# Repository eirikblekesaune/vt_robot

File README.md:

vt_robot
========

All robot patches and code for Verdensteatret

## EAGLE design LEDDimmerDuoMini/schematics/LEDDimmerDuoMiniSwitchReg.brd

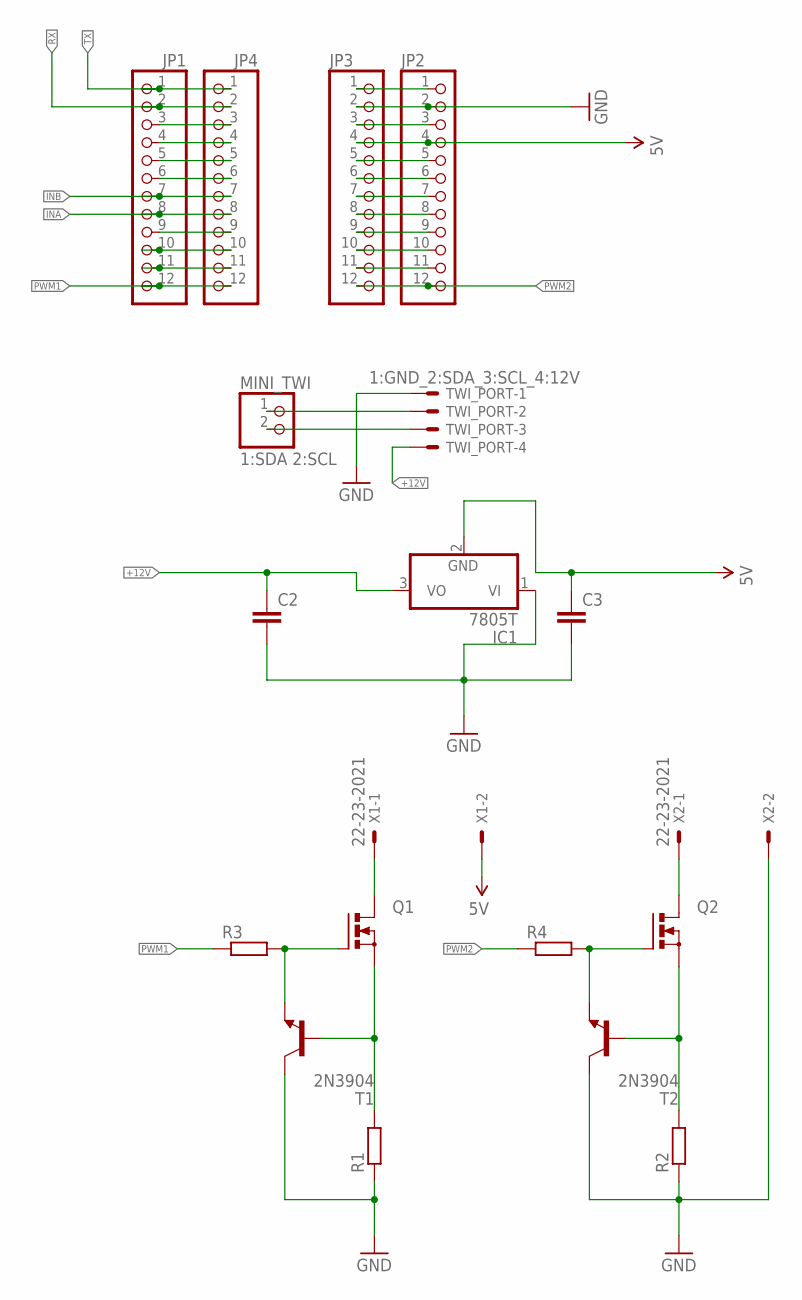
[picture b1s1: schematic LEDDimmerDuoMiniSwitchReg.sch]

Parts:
C2, C3: CAP0603-CAP; 0603-CAP
IC1: 7805T; TO220H
JP1, JP2, JP3, JP4: PINHD-1X12; 1X12
MINI_TWI: 1:SDA 2:SCL; 1X02
Q1, Q2: PMOSFET_NTO220BV; TO220BV
R1, R2: R-EU_VTA52; VTA52
R3, R4: R; R0805
T1, T2: 2N3904; TO92
TWI_PORT: 1:GND_2:SDA_3:SCL_4:12V; 22-23-2041
X1, X2: 22-23-2021

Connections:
5V: C3.1, IC1.2 (GND), JP2.4, JP3.4, X1.2
+12V: C2.1, IC1.3 (VO), TWI_PORT.4
GND: C2.2, C3.2, IC1.1 (VI), JP2.2, JP3.2, R1.1, R2.1, T1.1 (C), T2.1 (C), TWI_PORT.1, X2.2
INA: JP1.8, JP4.8
INB: JP1.7, JP4.7
unnamed: MINI_TWI.1, TWI_PORT.2
unnamed: MINI_TWI.2, TWI_PORT.3
unnamed: Q1.S, R1.2, T1.2 (B)
unnamed: Q2.S, R2.2, T2.2 (B)
unnamed: JP1.3, JP4.3
unnamed: Q2.G, R4.2, T2.3 (E)
unnamed: JP1.4, JP4.4
unnamed: JP1.5, JP4.5
unnamed: JP1.11, JP4.11
unnamed: JP1.10, JP4.10
unnamed: JP1.6, JP4.6
unnamed: JP1.9, JP4.9
unnamed: JP2.1, JP3.1
unnamed: JP2.3, JP3.3
unnamed: JP2.5, JP3.5
unnamed: JP2.6, JP3.6
unnamed: JP2.7, JP3.7
unnamed: JP2.8, JP3.8
unnamed: JP2.9, JP3.9
unnamed: JP2.10, JP3.10
unnamed: JP2.11, JP3.11
unnamed: Q1.D, X1.1
unnamed: Q2.D, X2.1
PWM1: JP1.12, JP4.12, Q1.G, R3.1, R3.2, T1.3 (E)
PWM2: JP2.12, JP3.12, R4.1
RX: JP1.2, JP4.2
TX: JP1.1, JP4.1

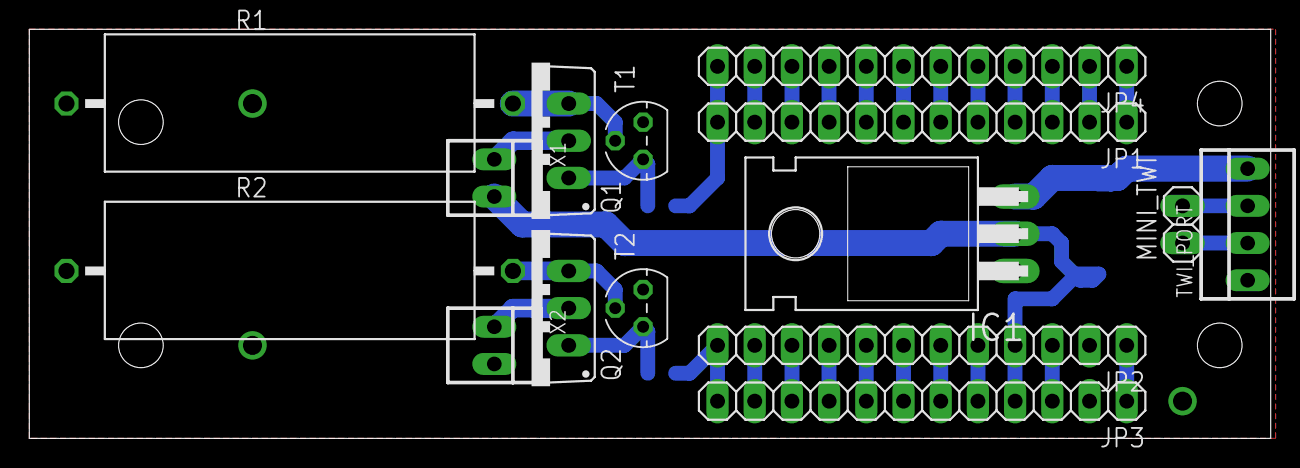
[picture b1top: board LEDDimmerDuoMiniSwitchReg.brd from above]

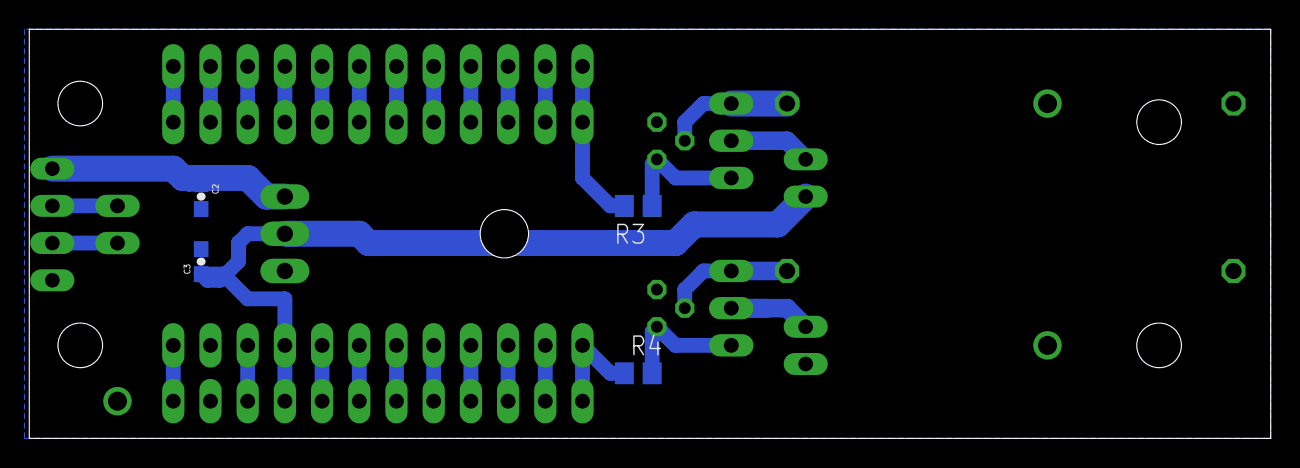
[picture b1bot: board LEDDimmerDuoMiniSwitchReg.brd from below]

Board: 2 copper layers, 84.8 x 27.9 mm, 19 parts (4 on the bottom side), 32 nets.

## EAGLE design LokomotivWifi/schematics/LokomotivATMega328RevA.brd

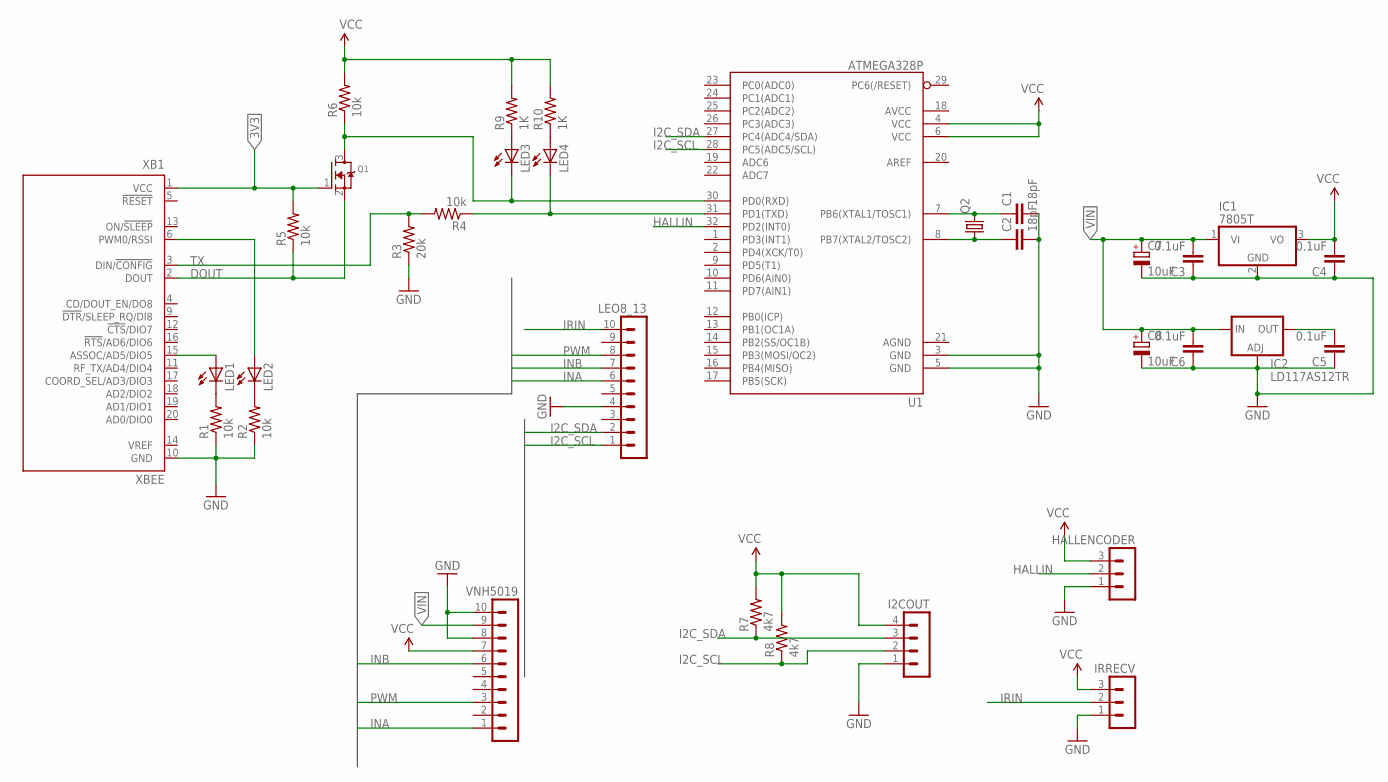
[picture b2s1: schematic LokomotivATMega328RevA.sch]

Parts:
C1, C2: 18pF; 0603-CAP
C3, C4, C5, C6: 0.1uF; 0603-CAP
C7, C8: 10uF; E3,5-10
HALLENCODER: MA03-1
I2COUT: MA04-1
IC1: 7805T; TO220H
IC2: LD117AS12TR; SOT223
IRRECV: MA03-1
LED1, LED2, LED3, LED4: LED-FKIT-1206; FKIT-LED-1206
LEO8_13: MA10-1
Q1: MOSFET-NREFLOW; SOT23
Q2: CRYSTALSM49; SM49
R1, R2, R4, R5, R6: 10k; R0805
R3: 20k; R0805
R7, R8: 4k7; R0805
R9, R10: 1K; R0805
U1: ATMEGA328P; TQFP32-08
VNH5019: MA10-1
XB1: XBEE

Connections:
3V3: Q1.1 (G), R5.2, XB1.1 (VCC)
DOUT: Q1.2 (S), R5.1, XB1.2 (DOUT)
GND: C1.2, C2.2, C3.1, C4.1, C5.1, C6.1, C7.-, C8.-, HALLENCODER.1, I2COUT.1, IC1.2 (GND), IC2.1 (ADJ), IRRECV.1, LEO8_13.4, R1.1, R2.1, R3.1, U1.3 (GND), U1.5 (GND), VNH5019.8, VNH5019.10, XB1.10 (GND)
HALLIN: HALLENCODER.2, U1.32 (PD2(INT0))
I2C_SCL: I2COUT.2, LEO8_13.1, R8.1, U1.28 (PC5(ADC5/SCL))
I2C_SDA: I2COUT.3, LEO8_13.2, R7.1, U1.27 (PC4(ADC4/SDA))
INA: LEO8_13.6, VNH5019.1
INB: LEO8_13.7, VNH5019.6
IRIN: IRRECV.2, LEO8_13.10
unnamed: LED1.C, R1.2
unnamed: LED2.C, R2.2
unnamed: LED1.A, XB1.15 (ASSOC/AD5/DIO5)
unnamed: LED2.A, XB1.6 (PWM0/RSSI)
unnamed: LED3.C, Q1.3 (D), R6.1, U1.30 (PD0(RXD))
unnamed: LED3.A, R9.1
unnamed: LED4.A, R10.1
unnamed: C1.1, Q2.2, U1.7 (PB6(XTAL1/TOSC1))
unnamed: LED4.C, R4.1, U1.31 (PD1(TXD))
unnamed: C2.1, Q2.1, U1.8 (PB7(XTAL2/TOSC2))
unnamed: C5.2, IC2.4 (OUT)
PWM: LEO8_13.8, VNH5019.3
TX: R3.2, R4.2, XB1.3 (DIN/!CONFIG)
VCC: C4.2, HALLENCODER.3, I2COUT.4, IC1.3 (VO), IRRECV.3, R6.2, R7.2, R8.2, R9.2, R10.2, U1.4 (VCC), U1.6 (VCC), VNH5019.7
VIN: C3.2, C6.2, C7.+, C8.+, IC1.1 (VI), IC2.3 (IN), VNH5019.9

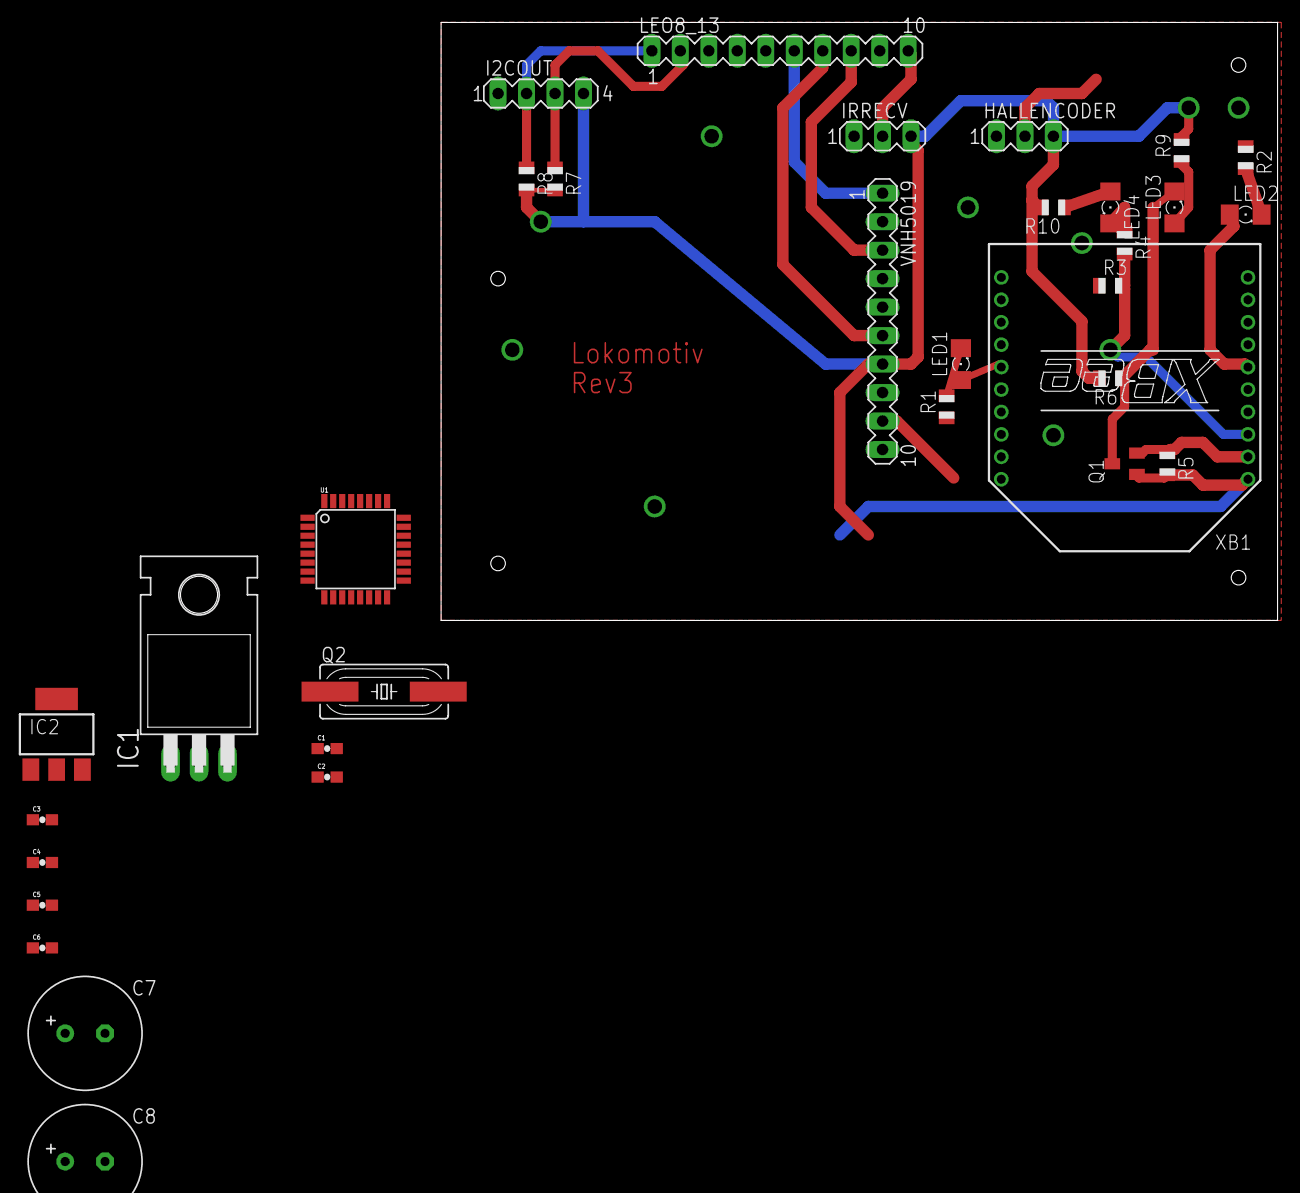
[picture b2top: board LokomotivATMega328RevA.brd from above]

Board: 2 copper layers, 74.6 x 53.3 mm, 33 parts (0 on the bottom side), 24 nets.

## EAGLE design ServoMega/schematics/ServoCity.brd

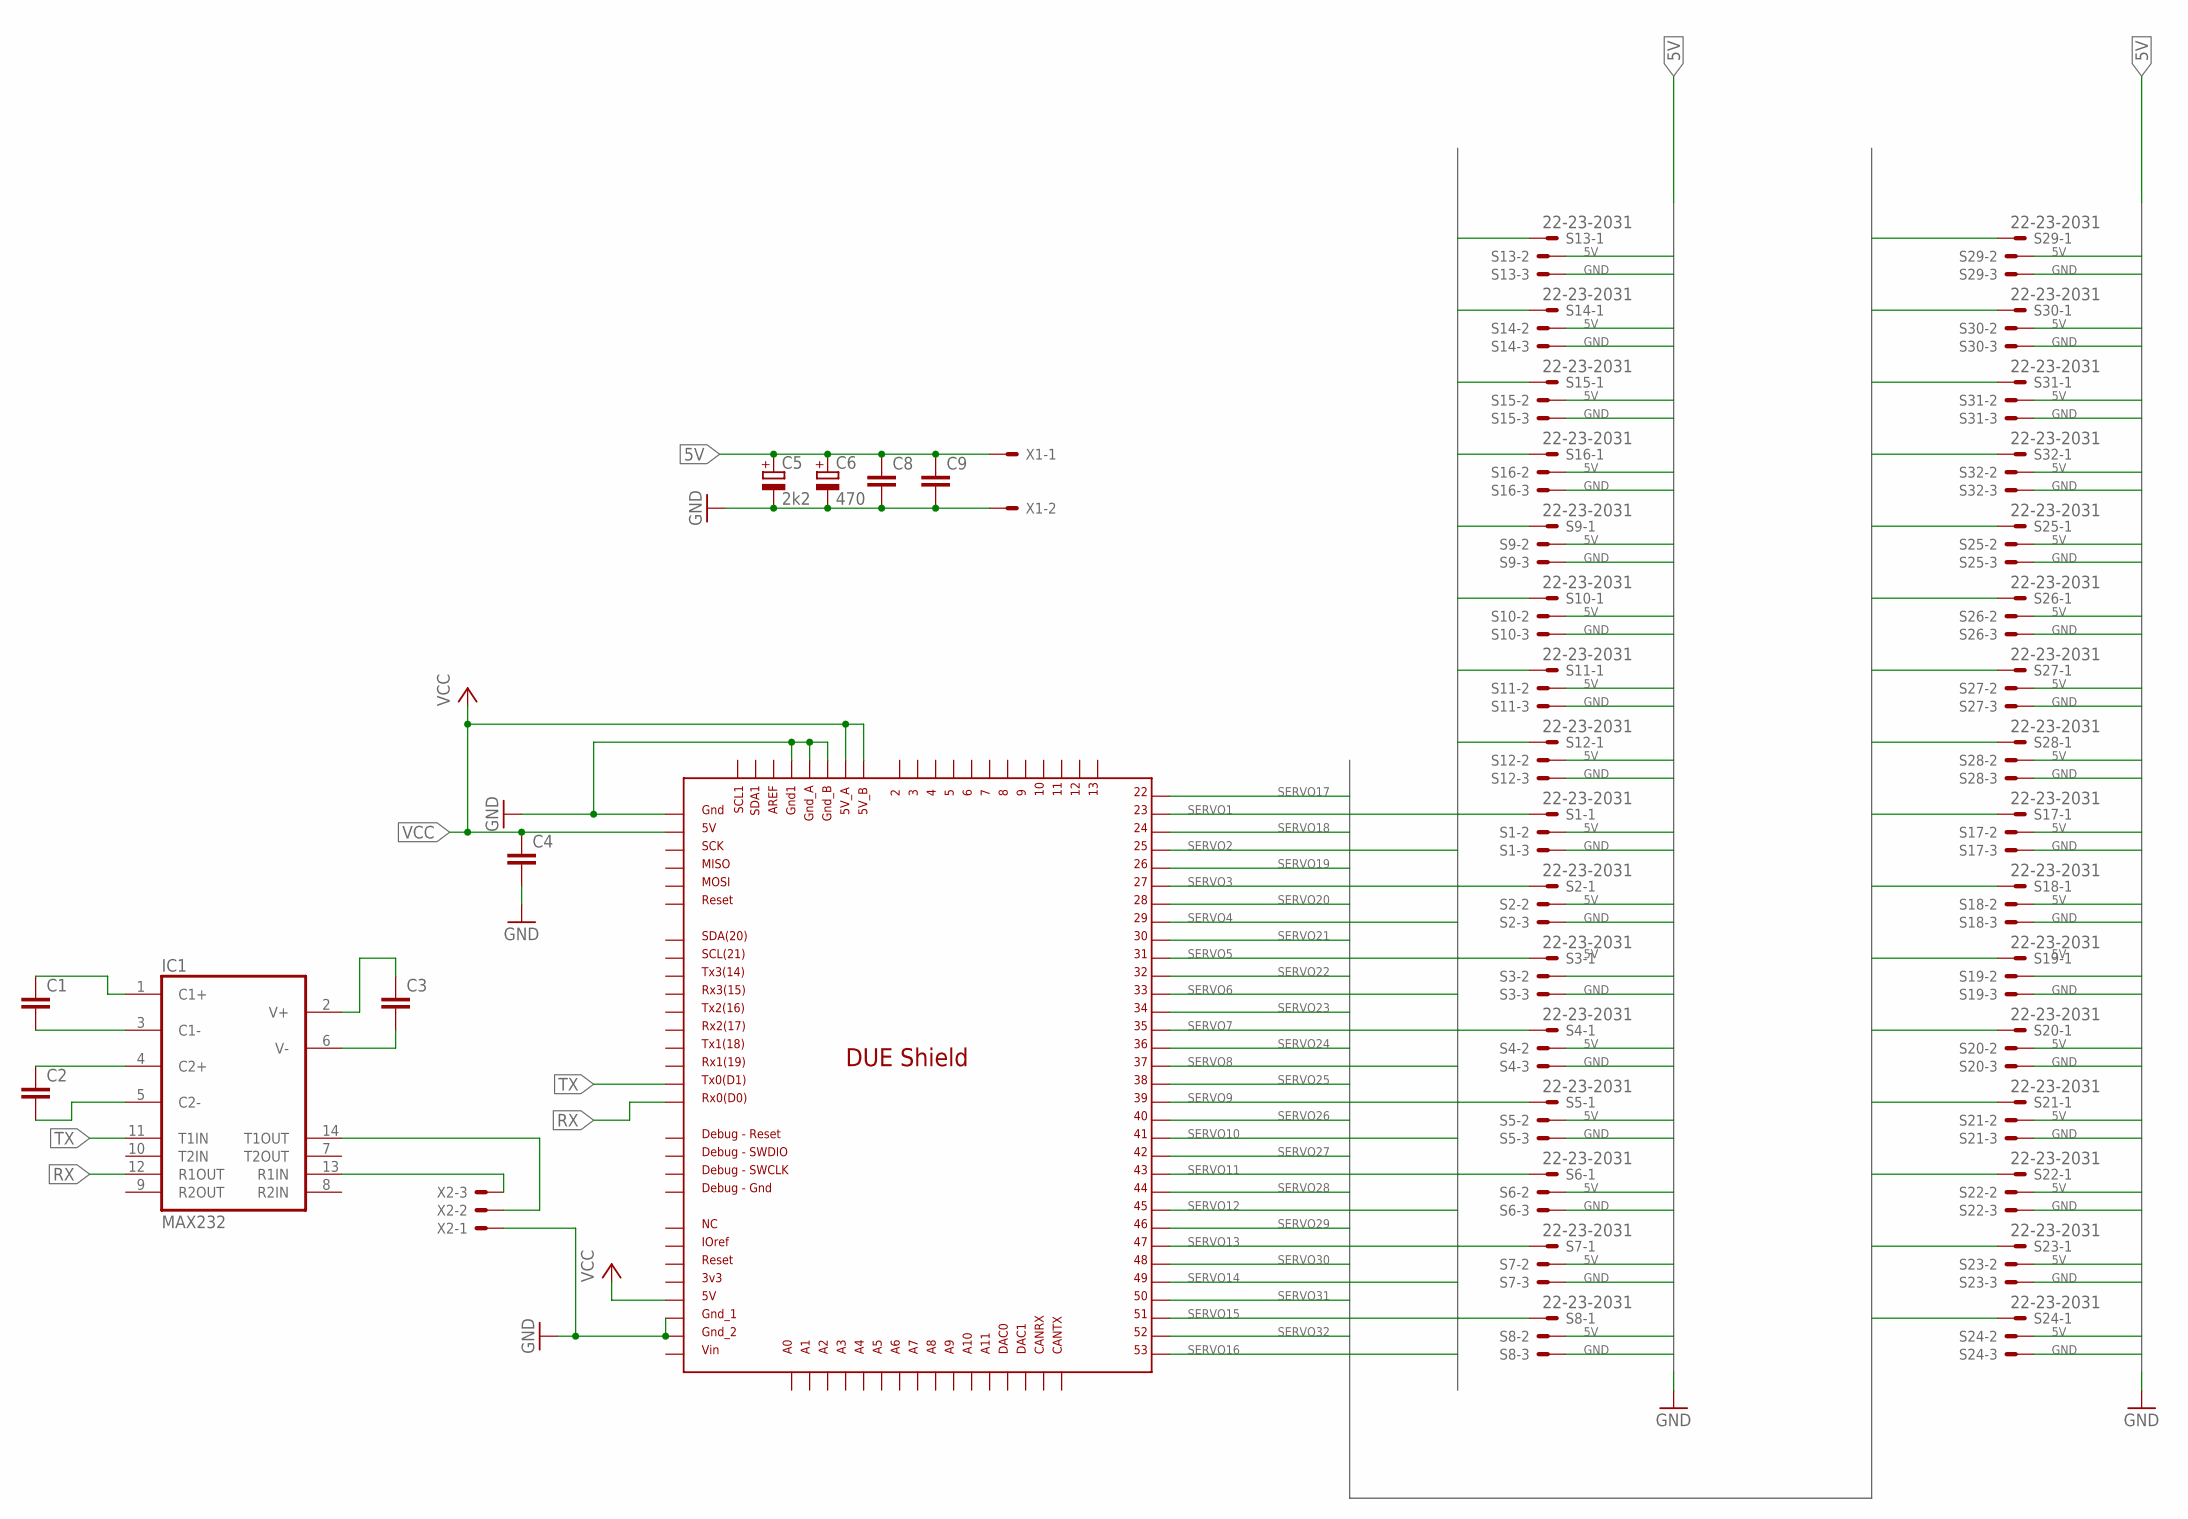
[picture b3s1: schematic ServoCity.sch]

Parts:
C1, C2, C3, C4: C-EUC0805; C0805
C5: 2k2; EB20D
C6: 470; E5-10,5
C8, C9: C; C0805
IC1: MAX232; DIL16
S1, S2, S3, S4, S5, S6, S7, S8, S9, S10, S11, S12, S13, S14, S15, S16, S17, S18, S19, S20, S21, S22, S23, S24, S25, S26, S27, S28, S29, S30, S31, S32: 22-23-2031
U$1: DUE(NORMAL)
X1: KK-156-2
X2: KK-156-3

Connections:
5V: C5.+, C6.+, C8.1, C9.1, S1.2, S2.2, S3.2, S4.2, S5.2, S6.2, S7.2, S8.2, S9.2, S10.2, S11.2, S12.2, S13.2, S14.2, S15.2, S16.2, S17.2, S18.2, S19.2, S20.2, S21.2, S22.2, S23.2, S24.2, S25.2, S26.2, S27.2, S28.2, S29.2, S30.2, S31.2, S32.2, X1.1
GND: C4.2, C5.-, C6.-, C8.2, C9.2, IC1.15 (GND), S1.3, S2.3, S3.3, S4.3, S5.3, S6.3, S7.3, S8.3, S9.3, S10.3, S11.3, S12.3, S13.3, S14.3, S15.3, S16.3, S17.3, S18.3, S19.3, S20.3, S21.3, S22.3, S23.3, S24.3, S25.3, S26.3, S27.3, S28.3, S29.3, S30.3, S31.3, S32.3, U$1.5V_ICSP, U$1.GND1, U$1.GND_1, U$1.GND_2, U$1.GND_A, U$1.GND_B, X1.2, X2.1
unnamed: IC1.14 (T1OUT), X2.2
unnamed: IC1.13 (R1IN), X2.3
unnamed: C1.1, IC1.1 (C1+)
unnamed: C1.2, IC1.3 (C1-)
unnamed: C2.1, IC1.4 (C2+)
unnamed: C2.2, IC1.5 (C2-)
unnamed: C3.1, IC1.2 (V+)
unnamed: C3.2, IC1.6 (V-)
RX: IC1.12 (R1OUT), U$1.RX0
SERVO1: S1.1, U$1.23
SERVO2: S2.1, U$1.25
SERVO3: S3.1, U$1.27
SERVO4: S4.1, U$1.29
SERVO5: S5.1, U$1.31
SERVO6: S6.1, U$1.33
SERVO7: S7.1, U$1.35
SERVO8: S8.1, U$1.37
SERVO9: S9.1, U$1.39
SERVO10: S10.1, U$1.41
SERVO11: S11.1, U$1.43
SERVO12: S12.1, U$1.45
SERVO13: S13.1, U$1.47
SERVO14: S14.1, U$1.49
SERVO15: S15.1, U$1.51
SERVO16: S16.1, U$1.53
SERVO17: S17.1, U$1.22
SERVO18: S18.1, U$1.24
SERVO19: S19.1, U$1.26
SERVO20: S20.1, U$1.28
SERVO21: S21.1, U$1.30
SERVO22: S22.1, U$1.32
SERVO23: S23.1, U$1.34
SERVO24: S24.1, U$1.36
SERVO25: S25.1, U$1.38
SERVO26: S26.1, U$1.40
SERVO27: S27.1, U$1.42
SERVO28: S28.1, U$1.44
SERVO29: S29.1, U$1.46
SERVO30: S30.1, U$1.48
SERVO31: S31.1, U$1.50
SERVO32: S32.1, U$1.52
TX: IC1.11 (T1IN), U$1.TX0
VCC: C4.1, IC1.16 (VCC), U$1.5V, U$1.5V_A, U$1.5V_B, U$1.GND_ICSP

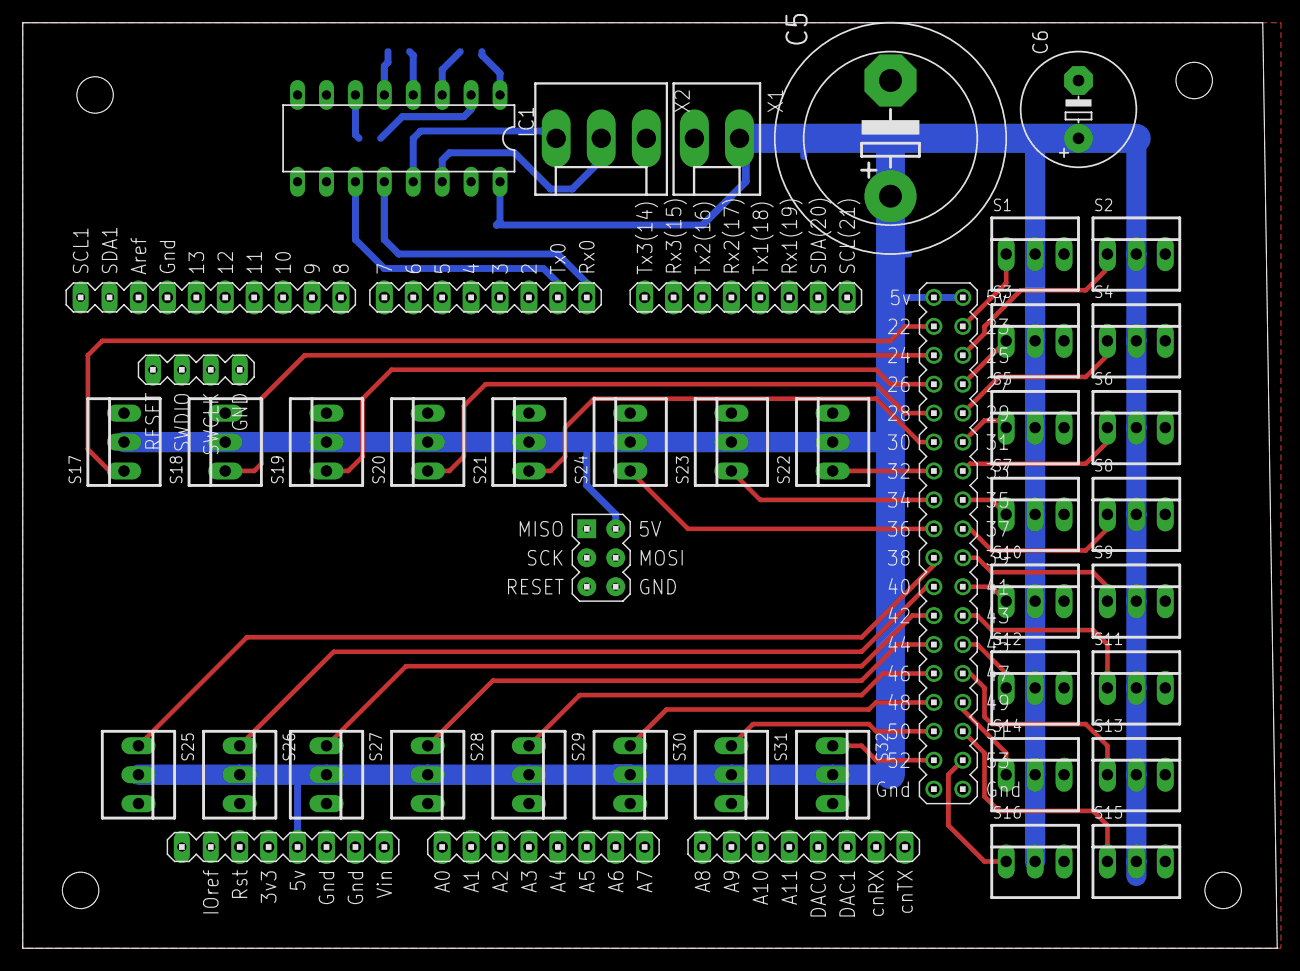
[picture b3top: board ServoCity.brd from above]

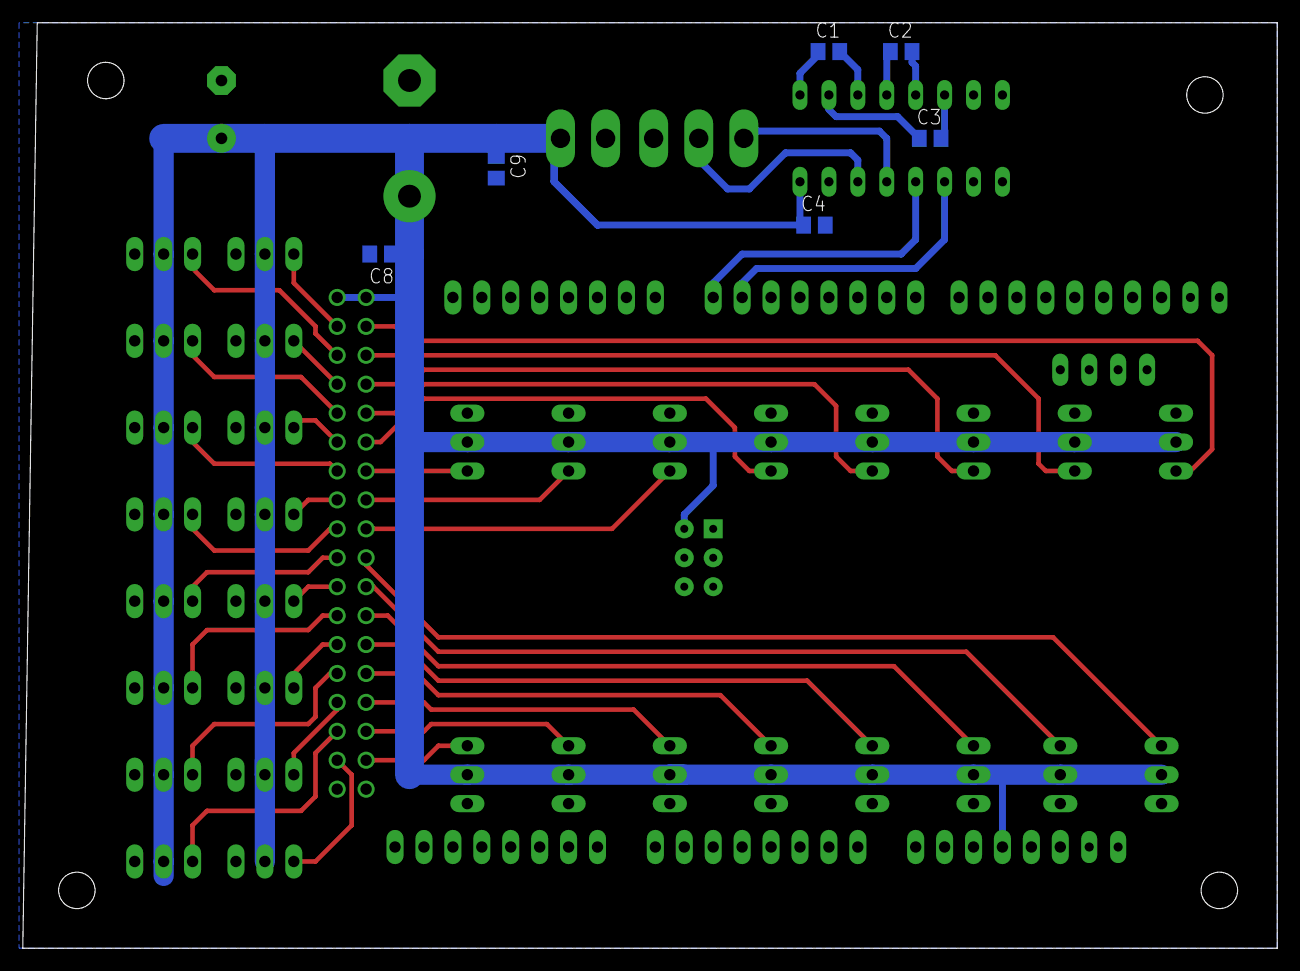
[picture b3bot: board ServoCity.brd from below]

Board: 2 copper layers, 110.2 x 81.3 mm, 44 parts (6 on the bottom side), 45 nets.

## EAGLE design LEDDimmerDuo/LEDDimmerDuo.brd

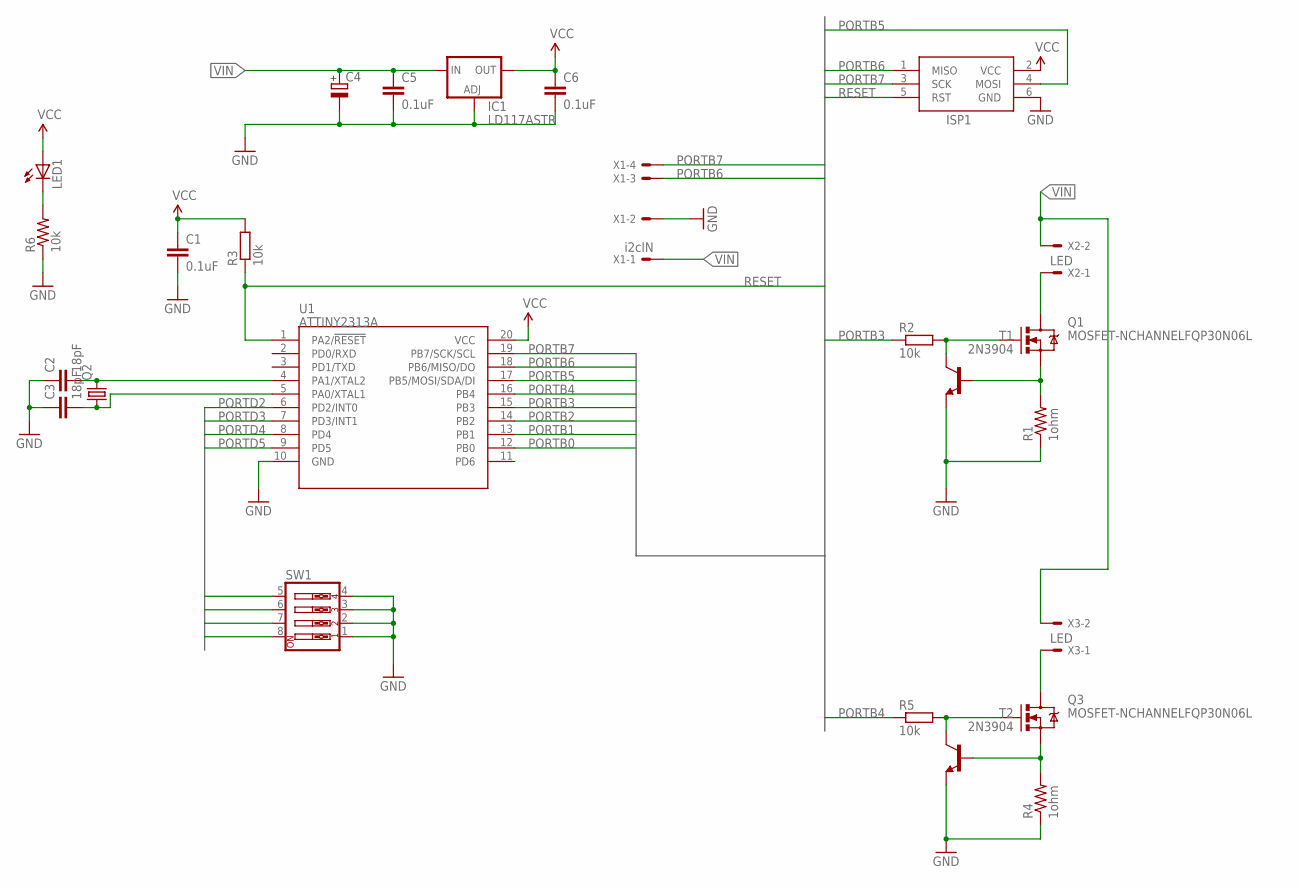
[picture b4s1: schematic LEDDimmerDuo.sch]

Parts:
C1, C5, C6: 0.1uF; 0805
C2, C3: 18pF; 0805
C4: CPOL-EUE3.5-10; E3,5-10
IC1: LD117ASTR; SOT223
ISP1: AVRISP-6; AVRISP
LED1: LED0603; LED-0603
Q1, Q3: MOSFET-NCHANNELFQP30N06L; TO220V
Q2: CRYSTALSM49; SM49
R1, R4: 1ohm; VTA54
R2, R3, R5: 10k; R0805
R6: 10k; R0603
SW1: SW_DIP-4; EDG-04
T1, T2: 2N3904; TO92
U1: ATTINY2313A; SOP20W
X1: i2cIN; 22-23-2041
X2, X3: LED; 22-23-2021

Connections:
GND: C1.2, C2.1, C3.1, C4.-, C5.2, C6.2, IC1.1 (ADJ), ISP1.6 (GND), R1.1, R4.1, R6.1, SW1.1, SW1.2, SW1.3, SW1.4, T1.3 (E), T2.3 (E), U1.10 (GND), X1.2
unnamed: Q1.1 (G), R2.2, T1.1 (C)
unnamed: C3.2, Q2.1, U1.5 (PA0/XTAL1)
unnamed: C2.2, Q2.2, U1.4 (PA1/XTAL2)
unnamed: Q1.3 (S), R1.2, T1.2 (B)
unnamed: Q1.2 (D), X2.1
unnamed: Q3.1 (G), R5.2, T2.1 (C)
unnamed: Q3.3 (S), R4.2, T2.2 (B)
unnamed: Q3.2 (D), X3.1
unnamed: LED1.C, R6.2
PORTB0: U1.12 (PB0)
PORTB1: U1.13 (PB1)
PORTB2: U1.14 (PB2)
PORTB3: R2.1, U1.15 (PB3)
PORTB4: R5.1, U1.16 (PB4)
PORTB5: ISP1.4 (MOSI), U1.17 (PB5/MOSI/SDA/DI)
PORTB6: ISP1.1 (MISO), U1.18 (PB6/MISO/DO), X1.3
PORTB7: ISP1.3 (SCK), U1.19 (PB7/SCK/SCL), X1.4
PORTD2: SW1.5, U1.6 (PD2/INT0)
PORTD3: SW1.6, U1.7 (PD3/INT1)
PORTD4: SW1.7, U1.8 (PD4)
PORTD5: SW1.8, U1.9 (PD5)
RESET: ISP1.5 (RST), R3.1, U1.1 (PA2/!RESET)
VCC: C1.1, C6.1, IC1.4 (OUT), ISP1.2 (VCC), LED1.A, R3.2, U1.20 (VCC)
VIN: C4.+, C5.1, IC1.3 (IN), X1.1, X2.2, X3.2

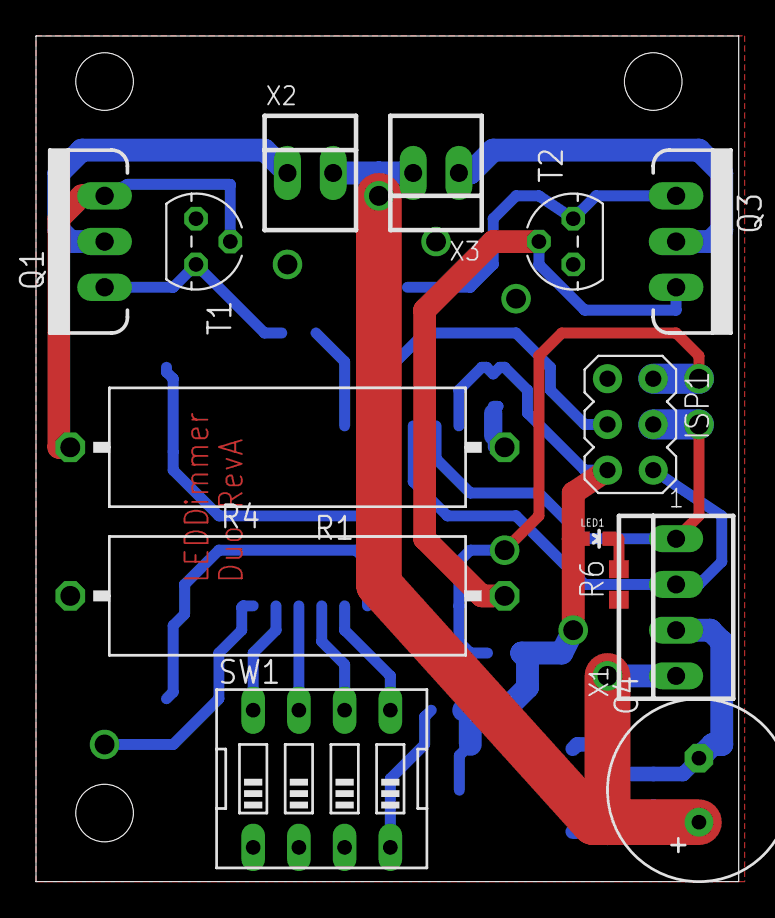
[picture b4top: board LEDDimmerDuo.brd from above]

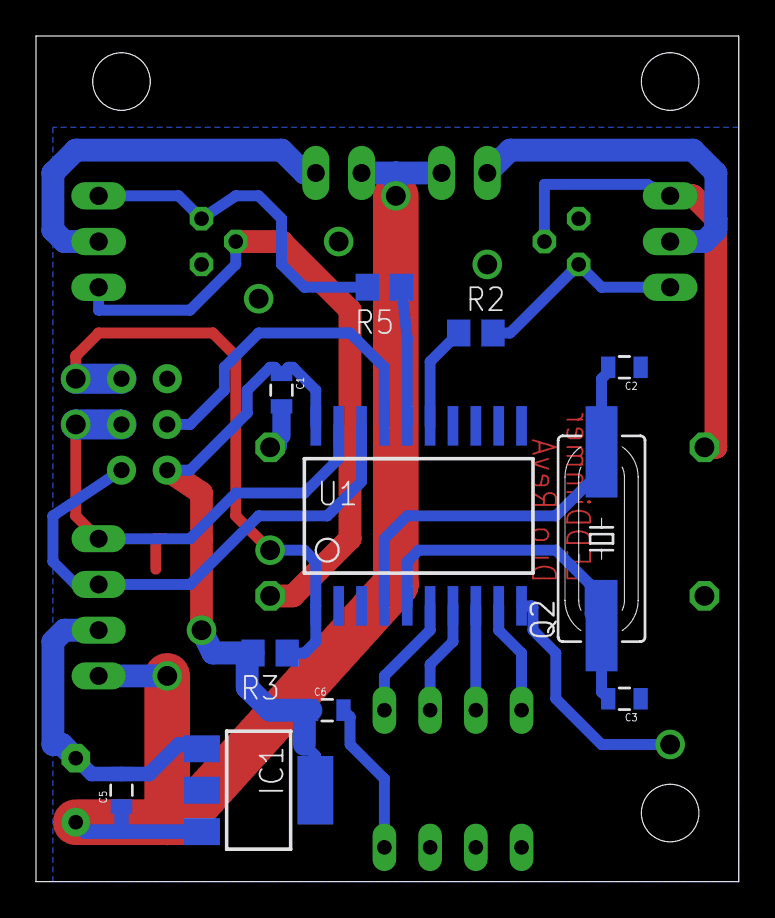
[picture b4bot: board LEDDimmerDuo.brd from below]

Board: 2 copper layers, 39.0 x 47.0 mm, 25 parts (11 on the bottom side), 22 nets.

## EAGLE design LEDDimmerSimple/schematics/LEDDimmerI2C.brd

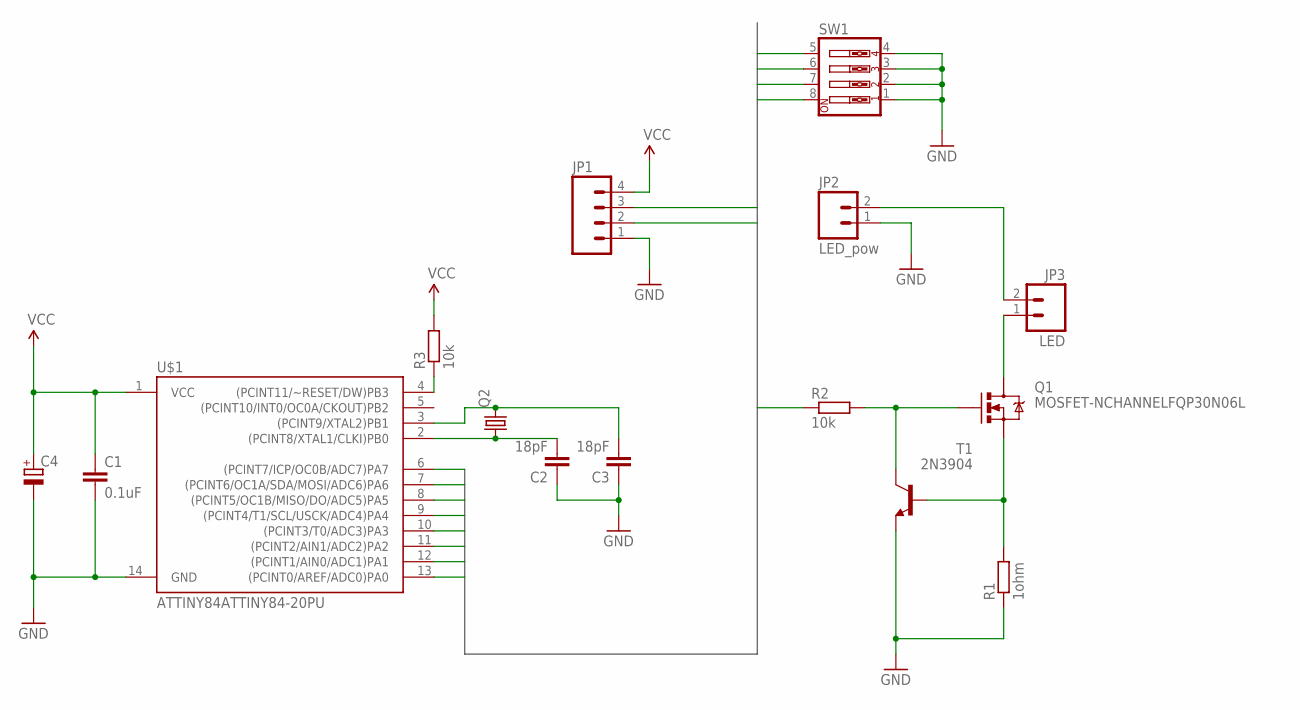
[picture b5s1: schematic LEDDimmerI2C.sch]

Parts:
C1: 0.1uF; 0805
C2, C3: 18pF; 0805
C4: CPOL-EUE3.5-10; E3,5-10
JP1: M04LONGPADS; 1X04_LONGPADS
JP2: LED_pow; 1X02_LONGPADS
JP3: LED; 1X02_LONGPADS
Q1: MOSFET-NCHANNELFQP30N06L; TO220V
Q2: CRYSTALSM49; SM49
R1: 1ohm; VMTB60
R2, R3: 10k; R0805
SW1: SW_DIP-4; EDG-04
T1: 2N3904; TO92
U$1: ATTINY84ATTINY84-20PU; DIL14

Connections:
GND: C1.2, C2.1, C3.1, C4.-, JP1.1, JP2.1, R1.1, SW1.1, SW1.2, SW1.3, SW1.4, T1.3 (E), U$1.14 (GND)
unnamed: Q1.1 (G), R2.2, T1.1 (C)
unnamed: R3.1, U$1.4 ((PCINT11/~RESET/DW)PB3)
unnamed: C3.2, Q2.2, U$1.3 ((PCINT9/XTAL2)PB1)
unnamed: C2.2, Q2.1, U$1.2 ((PCINT8/XTAL1/CLKI)PB0)
unnamed: Q1.3 (S), R1.2, T1.2 (B)
unnamed: JP2.2, JP3.2
unnamed: JP3.1, Q1.2 (D)
PORTA0: SW1.5, U$1.13 ((PCINT0/AREF/ADC0)PA0)
PORTA1: SW1.6, U$1.12 ((PCINT1/AIN0/ADC1)PA1)
PORTA2: SW1.7, U$1.11 ((PCINT2/AIN1/ADC2)PA2)
PORTA3: SW1.8, U$1.10 ((PCINT3/T0/ADC3)PA3)
PORTA4: JP1.2, U$1.9 ((PCINT4/T1/SCL/USCK/ADC4)PA4)
PORTA5: R2.1, U$1.8 ((PCINT5/OC1B/MISO/DO/ADC5)PA5)
PORTA6: JP1.3, U$1.7 ((PCINT6/OC1A/SDA/MOSI/ADC6)PA6)
PORTA7: U$1.6 ((PCINT7/ICP/OC0B/ADC7)PA7)
VCC: C1.1, C4.+, JP1.4, R3.2, U$1.1 (VCC)

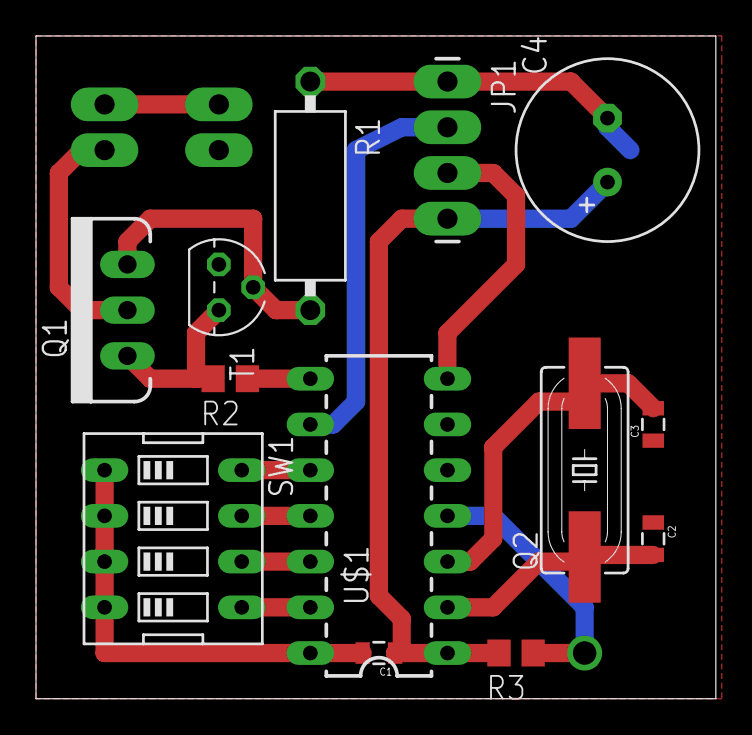
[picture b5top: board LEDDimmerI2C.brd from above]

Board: 2 copper layers, 37.8 x 36.8 mm, 15 parts (0 on the bottom side), 16 nets.

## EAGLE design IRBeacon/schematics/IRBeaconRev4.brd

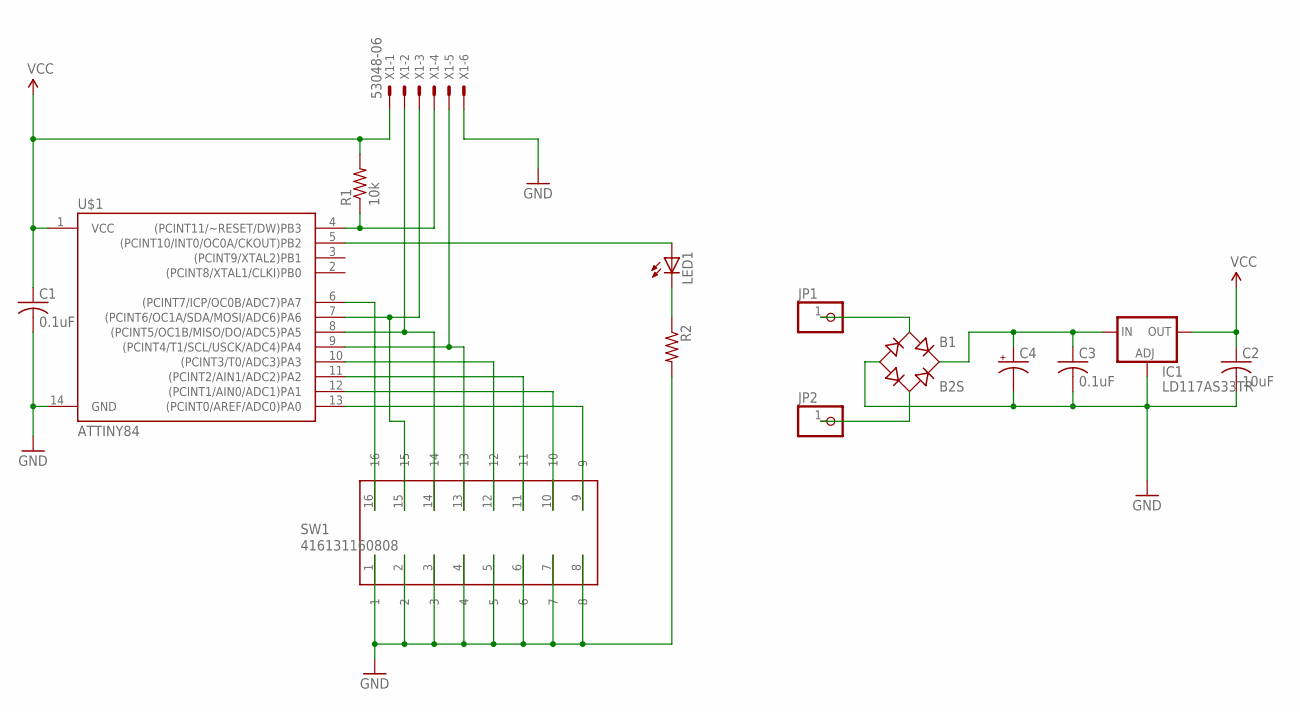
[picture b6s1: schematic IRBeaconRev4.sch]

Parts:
B1: B2S; MBS
C1, C3: 0.1uF; C0805
C2: 10uF; C0805
C4: CAP_POLPTH4; CPOL-RADIAL-1000UF-25V
IC1: LD117AS33TR; SOT223
JP1, JP2: PINHD-1X1; 1X01
LED1: LEDCHIPLED_1206; CHIPLED_1206
R1: 10k; R0805
R2: R-US_R0805; R0805
SW1: 416131160808
U$1: ATTINY84; SO14
X1: 53048-06

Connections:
GND: B1.-, C1.2, C2.2, C3.2, C4.2 (-), IC1.1 (ADJ), R2.2, SW1.1, SW1.2, SW1.3, SW1.4, SW1.5, SW1.6, SW1.7, SW1.8, U$1.14 (GND), X1.6
unnamed: R1.1, U$1.4 ((PCINT11/~RESET/DW)PB3), X1.4
unnamed: B1.AC2, JP2.1
unnamed: B1.+, C3.1, C4.1 (+), IC1.3 (IN)
unnamed: SW1.12, U$1.10 ((PCINT3/T0/ADC3)PA3)
unnamed: SW1.11, U$1.11 ((PCINT2/AIN1/ADC2)PA2)
unnamed: SW1.10, U$1.12 ((PCINT1/AIN0/ADC1)PA1)
unnamed: LED1.A, U$1.5 ((PCINT10/INT0/OC0A/CKOUT)PB2)
unnamed: SW1.13, U$1.9 ((PCINT4/T1/SCL/USCK/ADC4)PA4), X1.5
unnamed: SW1.9, U$1.13 ((PCINT0/AREF/ADC0)PA0)
unnamed: SW1.15, U$1.7 ((PCINT6/OC1A/SDA/MOSI/ADC6)PA6), X1.3
unnamed: SW1.14, U$1.8 ((PCINT5/OC1B/MISO/DO/ADC5)PA5), X1.2
unnamed: LED1.C, R2.1
unnamed: SW1.16, U$1.6 ((PCINT7/ICP/OC0B/ADC7)PA7)
RAIL_A: B1.AC1, JP1.1
VCC: C1.1, C2.1, IC1.4 (OUT), R1.2, U$1.1 (VCC), X1.1

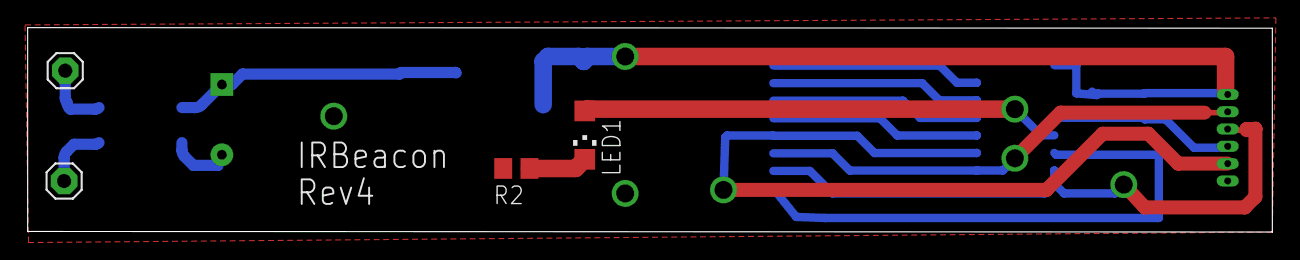
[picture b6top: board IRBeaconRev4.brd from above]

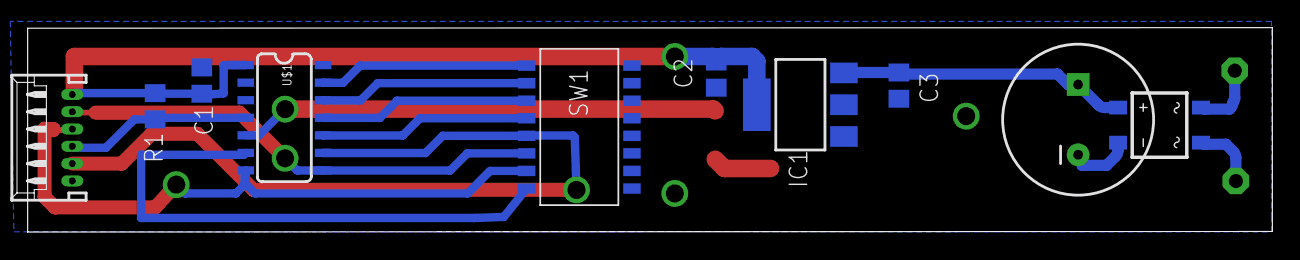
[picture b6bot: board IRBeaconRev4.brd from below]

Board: 2 copper layers, 90.0 x 14.8 mm, 14 parts (10 on the bottom side), 16 nets.

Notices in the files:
parts and their libraries:
DipSchalter: Copyright: Würth Elektronik
SparkFun-DigitalIC: Licensing: CC v3.0 Share-Alike You are welcome to use this library for commercial purposes.
